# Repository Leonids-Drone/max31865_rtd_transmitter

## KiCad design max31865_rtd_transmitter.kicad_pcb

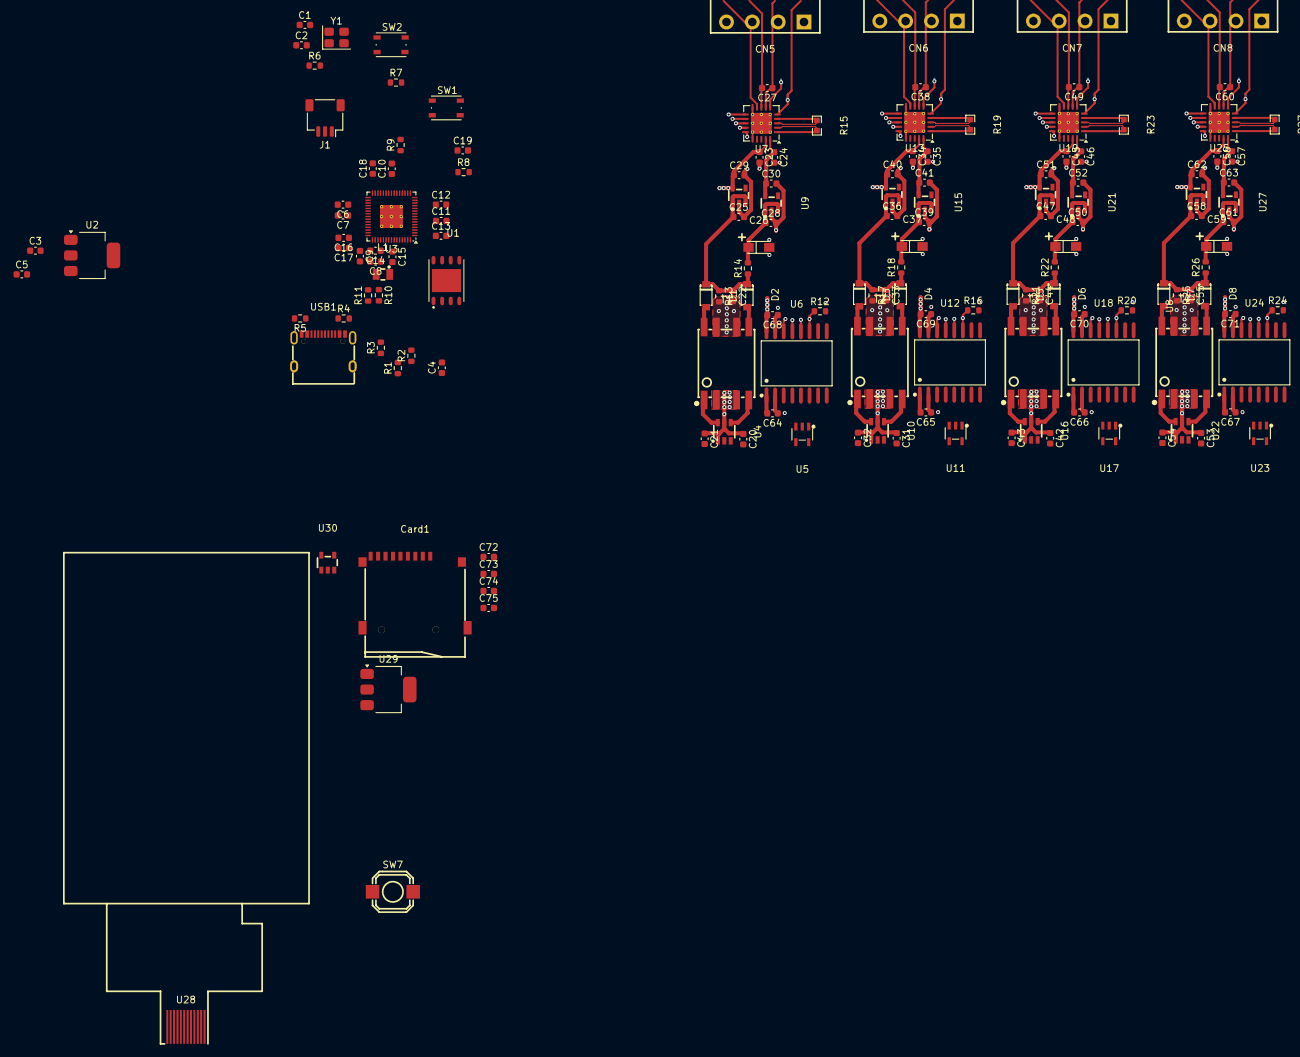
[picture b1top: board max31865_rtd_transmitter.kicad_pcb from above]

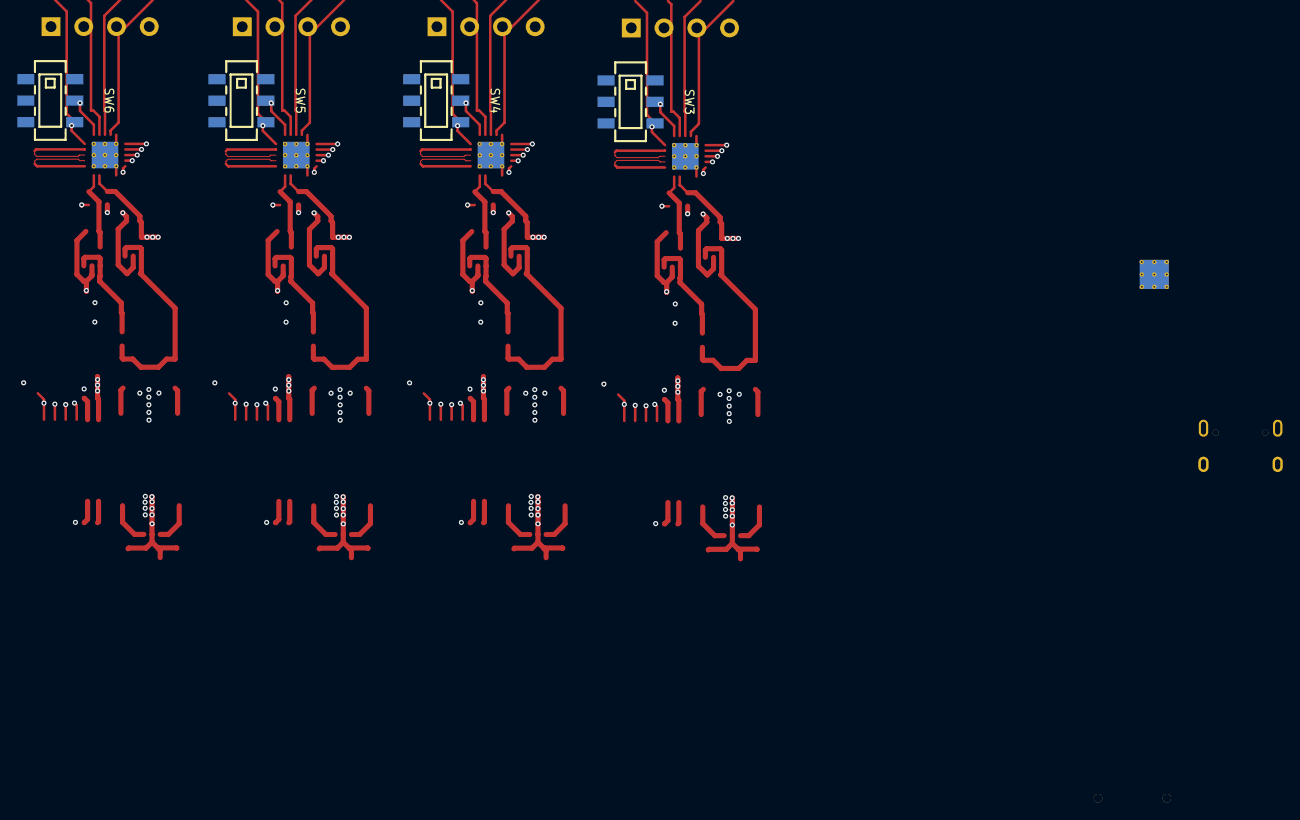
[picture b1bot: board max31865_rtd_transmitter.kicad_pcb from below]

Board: 4 copper layers, 160 parts (4 on the bottom side), 126 nets.

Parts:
C1, C2: 15p; C_0603_1608Metric
C3, C5, C19, C21, C32, C43, C54, C72, C73, C74: 10u; C_0603_1608Metric
C4, C8, C11, C12, C13, C14, C15, C16, C17, C18, C20, C23, C24, C31, C34, C35, C42, C45, C46, C53, C56, C57, C64, C65, C66, C67, C68, C69, C70, C71, C75: 100n; C_0603_1608Metric
C6, C7, C9, C10, C22, C33, C44, C55: 4.7u; C_0603_1608Metric
C25, C28, C29, C30, C36, C39, C40, C41, C47, C50, C51, C52, C58, C61, C62, C63: 1u; C_0603_1608Metric
C26, C37, C48, C59: TAJA106K016RNJ; CAP-SMD_L3.2-W1.6-RD-C7171
C27, C38, C49, C60: 10n; C_0603_1608Metric
CN5, CN6, CN7, CN8: WJ15EDGRC-3.81-4P; CONN-TH_WJ15EDGRC-3.81-4P
Card1: TF-01A; TF-SMD_TF-01A
D1, D2, D3, D4, D5, D6, D7, D8: RB160M-30TR; SOD-123_L2.8-W1.8-LS3.7-RD
J1: SM03B-SRSS-TB; JST_SH_SM03B-SRSS-TB_1x03-1MP_P1.00mm_Horizontal
L1: AOTA-B201610S3R3-101-T; IND-SMD_L2.0-W1.6_AOTA-B201610S3R3-101-T
R1, R3: DNF; R_0603_1608Metric
R2: 0; R_0603_1608Metric
R4, R5: 5.1k; R_0603_1608Metric
R6, R7, R9: 1k; R_0603_1608Metric
R8: 33; R_0603_1608Metric
R10, R11: 27; R_0603_1608Metric
R12, R16, R20, R24: 47k; R_0603_1608Metric
R13, R17, R21, R25: 4.7k; R_0603_1608Metric
R14, R18, R22, R26: 2.2; R_0603_1608Metric
R15, R19, R23, R27: PTFR0603B4K30P9; R0603
SW1, SW2: SW_Push; SW_Push_1P1T_NO_Vertical_Wuerth_434133025816
SW3, SW4, SW5, SW6: MST22D18G2; SW-SMD_MST22D18G2
SW7: OS4D501110; SW-SMD_L6.0-W6.0-P6.00-LS6.8
T1, T2, T3, T4: VPT87BB-01B; XFMR-SMD_VPSC_VPT87BB
U1: W25Q32JVZPIQ; WSON-8_L6.0-W5.0-P1.27-BL-EP
U2, U29: NCP1117-3.3_SOT223; SOT-223-3_TabPin2
U3: RP2350_60QFN; QFN-60-1EP_7x7mm_P0.4mm_EP3.4x3.4mm_ThermalVias
U4, U10, U16, U22: VPS8504B; SOT-23-6_L2.9-W1.6-P0.95-LS2.8-BR
U5, U11, U17, U23: SN74LVC1G125DBVR; SOT-23-5_L3.0-W1.7-P0.95-LS2.8-BL
U6, U12, U18, U24: ISO7741DWR; SOIC-16_L10.3-W7.5-P1.27-LS10.3-BL
U7, U13, U19, U25: MAX31865xTP; TQFN-20-1EP_5x5mm_P0.65mm_EP3.1x3.1mm_ThermalVias
U8, U9, U14, U15, U20, U21, U26, U27: TPS7A2033PDBVR; SOT-23-5_L2.9-W1.6-P0.95-LS2.8-BR
U28: HS20HS072RX; OLED-SMD_HS20HS072RX
U30: LGS63042; SOT-23-5_L2.9-W1.6-P0.95-LS2.8-BL
USB1: TYPE-C 16PIN 2MD(073); USB-C-SMD_TYPE-C-6PIN-2MD-073
Y1: ABM8-272-T3; Crystal_SMD_3225-4Pin_3.2x2.5mm

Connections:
+1V1: C7.1, C8.1, C10.1, C11.1, L1.2, U3.6 (DVDD), U3.23 (DVDD), U3.39 (DVDD), U3.50 (VREG_FB)
+3V3: C4.1, C5.1, C6.1, C12.1, C13.1, C14.1, C15.1, C16.1, C17.1, C18.1, C19.1, R3.1, R8.1, U1.8 (VCC), U2.2 (VO), U3.1 (IOVDD), U3.11 (IOVDD), U3.20 (IOVDD), U3.30 (IOVDD), U3.38 (IOVDD), U3.44 (ADC_AVDD), U3.45 (IOVDD), U3.49 (VREG_VIN), U3.53 (USB_OTP_VDD), U3.54 (QSPI_IOVDD)
+5V: C20.1, C21.1, C31.1, C32.1, C42.1, C43.1, C53.1, C54.1, C64.2, C65.2, C66.2, C67.2, T1.2, T1.3, T2.2, T2.3, T3.2, T3.3, T4.2, T4.3, U4.1 (EN), U4.5 (VIN), U5.5 (VCC), U6.1 (VCC1), U6.7 (EN1), U10.1 (EN), U10.5 (VIN), U11.5 (VCC), U12.1 (VCC1), U12.7 (EN1), U16.1 (EN), U16.5 (VIN), U17.5 (VCC), U18.1 (VCC1), U18.7 (EN1), U22.1 (EN), U22.5 (VIN), U23.5 (VCC), U24.1 (VCC1), U24.7 (EN1)
/31865_ch0/CH_SDO_LOWZ: U5.2 (A), U6.6 (OUTD)
/31865_ch0/V_trans: C22.1, C25.1, D1.1, D2.1, R13.1, R14.1, U8.1 (IN), U8.3 (EN)
/31865_ch0/force2: SW3.2, U7.6 (FORCE2)
/31865_ch0/force+: CN5.1, SW3.3, U7.5 (FORCE+)
/31865_ch0/local_3v3_analog: C24.1, C30.1, U7.20 (VDD), U9.5 (OUT)
/31865_ch0/local_3v3_digital: C23.1, C23.2, C29.1, C68.2, U6.10 (EN2), U6.16 (VCC2), U7.19 (DVDD), U8.5 (OUT)
/31865_ch0/local_gnd: C22.2, C25.2, C26.2, C28.2, C29.2, C30.2, C68.1, R12.2, R13.2, T1.6, T1.7, U6.9 (GND2), U6.15 (GND2), U7.15 (DGND), U8.2 (GND), U9.2 (GND)
/31865_ch0/local_gnd_analog: C24.2, SW3.1, U7.10 (GND), U7.16 (GND), U7.21 (GND)
/31865_ch1/CH_SDO_LOWZ: U11.2 (A), U12.6 (OUTD)
/31865_ch1/V_trans: C33.1, C36.1, D3.1, D4.1, R17.1, R18.1, U14.1 (IN), U14.3 (EN)
/31865_ch1/force2: SW4.2, U13.6 (FORCE2)
/31865_ch1/force+: CN6.1, SW4.3, U13.5 (FORCE+)
/31865_ch1/local_3v3_analog: C35.1, C41.1, U13.20 (VDD), U15.5 (OUT)
/31865_ch1/local_3v3_digital: C34.1, C34.2, C40.1, C69.2, U12.10 (EN2), U12.16 (VCC2), U13.19 (DVDD), U14.5 (OUT)
/31865_ch1/local_gnd: C33.2, C36.2, C37.2, C39.2, C40.2, C41.2, C69.1, R16.2, R17.2, T2.6, T2.7, U12.9 (GND2), U12.15 (GND2), U13.15 (DGND), U14.2 (GND), U15.2 (GND)
/31865_ch1/local_gnd_analog: C35.2, SW4.1, U13.10 (GND), U13.16 (GND), U13.21 (GND)
/31865_ch2/CH_SDO_LOWZ: U17.2 (A), U18.6 (OUTD)
/31865_ch2/V_trans: C44.1, C47.1, D5.1, D6.1, R21.1, R22.1, U20.1 (IN), U20.3 (EN)
/31865_ch2/force2: SW5.2, U19.6 (FORCE2)
/31865_ch2/force+: CN7.1, SW5.3, U19.5 (FORCE+)
/31865_ch2/local_3v3_analog: C46.1, C52.1, U19.20 (VDD), U21.5 (OUT)
/31865_ch2/local_3v3_digital: C45.1, C45.2, C51.1, C70.2, U18.10 (EN2), U18.16 (VCC2), U19.19 (DVDD), U20.5 (OUT)
/31865_ch2/local_gnd: C44.2, C47.2, C48.2, C50.2, C51.2, C52.2, C70.1, R20.2, R21.2, T3.6, T3.7, U18.9 (GND2), U18.15 (GND2), U19.15 (DGND), U20.2 (GND), U21.2 (GND)
/31865_ch2/local_gnd_analog: C46.2, SW5.1, U19.10 (GND), U19.16 (GND), U19.21 (GND)
/31865_ch3/CH_SDO_LOWZ: U23.2 (A), U24.6 (OUTD)
/31865_ch3/V_trans: C55.1, C58.1, D7.1, D8.1, R25.1, R26.1, U26.1 (IN), U26.3 (EN)
/31865_ch3/force2: SW6.2, U25.6 (FORCE2)
/31865_ch3/force+: CN8.1, SW6.3, U25.5 (FORCE+)
/31865_ch3/local_3v3_analog: C57.1, C63.1, U25.20 (VDD), U27.5 (OUT)
/31865_ch3/local_3v3_digital: C56.1, C56.2, C62.1, C71.2, U24.10 (EN2), U24.16 (VCC2), U25.19 (DVDD), U26.5 (OUT)
/31865_ch3/local_gnd: C55.2, C58.2, C59.2, C61.2, C62.2, C63.2, C71.1, R24.2, R25.2, T4.6, T4.7, U24.9 (GND2), U24.15 (GND2), U25.15 (DGND), U26.2 (GND), U27.2 (GND)
/31865_ch3/local_gnd_analog: C57.2, SW6.1, U25.10 (GND), U25.16 (GND), U25.21 (GND)
/rp2350/FLASH_SS: R1.2, R2.2, R3.2, U1.1 (/CS)
/rp2350/GPIO0: R1.1, U3.2 (GPIO0)
/rp2350/GPIO2: U3.4 (GPIO2), U6.4 (INB), U12.4 (INB), U18.4 (INB), U24.4 (INB)
/rp2350/GPIO3: U3.5 (GPIO3), U6.3 (INA), U12.3 (INA), U18.3 (INA), U24.3 (INA)
/rp2350/GPIO4: U3.7 (GPIO4), U5.4 (Y), U11.4 (Y), U17.4 (Y), U23.4 (Y)
/rp2350/GPIO5: U3.8 (GPIO5), U5.1 (~OE), U6.5 (INC)
/rp2350/GPIO6: U3.9 (GPIO6), U11.1 (~OE), U12.5 (INC)
/rp2350/GPIO7: U3.10 (GPIO7), U17.1 (~OE), U18.5 (INC)
/rp2350/GPIO8: U3.12 (GPIO8), U23.1 (~OE), U24.5 (INC)
/rp2350/QSPI_SCLK: U1.6 (CLK), U3.56 (QSPI_SCLK)
/rp2350/QSPI_SD0: U1.5 (DI(IO0)), U3.57 (QSPI_SD0)
/rp2350/QSPI_SD1: U1.2 (DO(IO1)), U3.59 (QSPI_SD1)
/rp2350/QSPI_SD2: U1.3 (/WP(IO2)), U3.58 (QSPI_SD2)
/rp2350/QSPI_SD3: U1.7 (/HOLDor/RESET(IO3)), U3.55 (QSPI_SD3)
/rp2350/QSPI_SS: R2.1, R9.1, U3.60 (QSPI_SS)
/rp2350/RUN: SW2.2, U3.26 (RUN)
/rp2350/SWCLK: J1.1, U3.24 (SWCLK)
/rp2350/SWD: J1.3, U3.25 (SWD)
/rp2350/USB_D+: R10.1, USB1.6 (DP1), USB1.8 (DP2)
/rp2350/USB_D-: R11.1, USB1.5 (DN2), USB1.7 (DN1)
/rp2350/VREG_AVDD: C9.1, R8.2, U3.46 (VREG_AVDD)
/rp2350/VREG_LX: L1.1, U3.48 (VREG_LX)
/rp2350/XIN: C1.1, U3.21 (XIN), Y1.1
/rp2350/XOUT: R6.1, U3.22 (XOUT)
/rp2350/~USB_BOOT: R9.2, SW1.2
/tf_sd_card/3v3_sd: C73.1, C74.1, C75.1, Card1.4 (VDD), U29.2 (VO)
Earth: Card1.10 (GND), Card1.11 (GND), Card1.12 (GND), Card1.13 (GND), USB1.13 (SHELL), USB1.14 (SHELL)
GND: C1.2, C2.2, C3.2, C4.2, C5.2, C6.2, C7.2, C8.2, C9.2, C10.2, C11.2, C12.2, C13.2, C14.2, C15.2, C16.2, C17.2, C18.2, C19.2, C20.2, C21.2, C31.2, C32.2, C42.2, C43.2, C53.2, C54.2, C64.1, C65.1, C66.1, C67.1, C72.2, C73.2, C74.2, C75.2, Card1.6 (VSS), J1.2, J1.MP (MountPin), R4.2, R5.2, R7.2, SW1.1, U1.4 (GND), U1.9 (EP), U2.1 (GND), U3.47 (VREG_PGND), U3.61 (GND), U4.2 (GND), U5.3 (GND), U6.2 (GND1), U6.8 (GND1), U10.2 (GND), U11.3 (GND), U12.2 (GND1), U12.8 (GND1), U16.2 (GND), U17.3 (GND), U18.2 (GND1), U18.8 (GND1), U22.2 (GND), U23.3 (GND), U24.2 (GND1), U24.8 (GND1), U29.1 (GND), USB1.1 (GND), USB1.12 (GND), Y1.2, Y1.4
unnamed: C2.1, R6.2, Y1.3
unnamed: D1.2, T1.8
unnamed: D2.2, T1.5
unnamed: D3.2, T2.8
unnamed: D4.2, T2.5
unnamed: D5.2, T3.8
unnamed: D6.2, T3.5
unnamed: D7.2, T4.8
unnamed: D8.2, T4.5
unnamed: R7.1, SW2.1
unnamed: R11.2, U3.51 (USB_DM)
unnamed: R10.2, U3.52 (USB_DP)
unnamed: T1.1, U4.6 (VD1)
unnamed: T1.4, U4.4 (VD2)
unnamed: R12.1, U6.11 (IND), U7.14 (SDO)
unnamed: U6.14 (OUTA), U7.11 (SDI)
unnamed: U6.13 (OUTB), U7.12 (SCLK)
unnamed: U6.12 (OUTC), U7.13 (~CS)
unnamed: R15.2, U7.1 (BIAS), U7.2 (REFIN+)
unnamed: CN5.4, U7.9 (FORCE-)
unnamed: R15.1, U7.3 (REFIN-), U7.4 (ISENSOR)
unnamed: C27.1, CN5.2, U7.7 (RTDIN+)
unnamed: C27.2, CN5.3, U7.8 (RTDIN-)
unnamed: C26.1, C28.1, R14.2, U9.1 (IN), U9.3 (EN)
unnamed: T2.1, U10.6 (VD1)
unnamed: T2.4, U10.4 (VD2)
unnamed: R16.1, U12.11 (IND), U13.14 (SDO)
unnamed: U12.14 (OUTA), U13.11 (SDI)
unnamed: U12.13 (OUTB), U13.12 (SCLK)
unnamed: U12.12 (OUTC), U13.13 (~CS)
unnamed: R19.2, U13.1 (BIAS), U13.2 (REFIN+)
unnamed: CN6.4, U13.9 (FORCE-)
unnamed: R19.1, U13.3 (REFIN-), U13.4 (ISENSOR)
unnamed: C38.1, CN6.2, U13.7 (RTDIN+)
unnamed: C38.2, CN6.3, U13.8 (RTDIN-)
unnamed: C37.1, C39.1, R18.2, U15.1 (IN), U15.3 (EN)
unnamed: T3.1, U16.6 (VD1)
unnamed: T3.4, U16.4 (VD2)
unnamed: R20.1, U18.11 (IND), U19.14 (SDO)
unnamed: U18.14 (OUTA), U19.11 (SDI)
unnamed: U18.13 (OUTB), U19.12 (SCLK)
unnamed: U18.12 (OUTC), U19.13 (~CS)
unnamed: R23.2, U19.1 (BIAS), U19.2 (REFIN+)
unnamed: CN7.4, U19.9 (FORCE-)
unnamed: R23.1, U19.3 (REFIN-), U19.4 (ISENSOR)
unnamed: C49.1, CN7.2, U19.7 (RTDIN+)
unnamed: C49.2, CN7.3, U19.8 (RTDIN-)
unnamed: C48.1, C50.1, R22.2, U21.1 (IN), U21.3 (EN)
unnamed: T4.1, U22.6 (VD1)
unnamed: T4.4, U22.4 (VD2)
unnamed: R24.1, U24.11 (IND), U25.14 (SDO)
unnamed: U24.14 (OUTA), U25.11 (SDI)
unnamed: U24.13 (OUTB), U25.12 (SCLK)
unnamed: U24.12 (OUTC), U25.13 (~CS)
unnamed: R27.2, U25.1 (BIAS), U25.2 (REFIN+)
unnamed: CN8.4, U25.9 (FORCE-)
unnamed: R27.1, U25.3 (REFIN-), U25.4 (ISENSOR)
unnamed: C60.1, CN8.2, U25.7 (RTDIN+)
unnamed: C60.2, CN8.3, U25.8 (RTDIN-)
unnamed: C59.1, C61.1, R26.2, U27.1 (IN), U27.3 (EN)
unnamed: R5.1, USB1.4 (CC1)
unnamed: R4.1, USB1.10 (CC2)
VBUS: C3.1, C72.1, U2.3 (VI), U29.3 (VI), USB1.2 (VBUS), USB1.11 (VBUS)

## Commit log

2026-02-11 Add gitignore for kicad
2026-02-11 Create kicad project, add resistor R0603
2026-02-19 Add isolated power and LDO
2026-03-02 Complete single channel design, add rp2350
2026-03-09 complete schematic layout
2026-03-10 complete component alignment
2026-03-10 Complete max31865 power supply and analog component layout
2026-03-11 start pcb layout, add sd card and screen
2026-03-23 Complete single channel design
